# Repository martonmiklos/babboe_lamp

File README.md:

# Babboe lamp replacement board

Heavily overengineered replacement board for Babboe headlight.

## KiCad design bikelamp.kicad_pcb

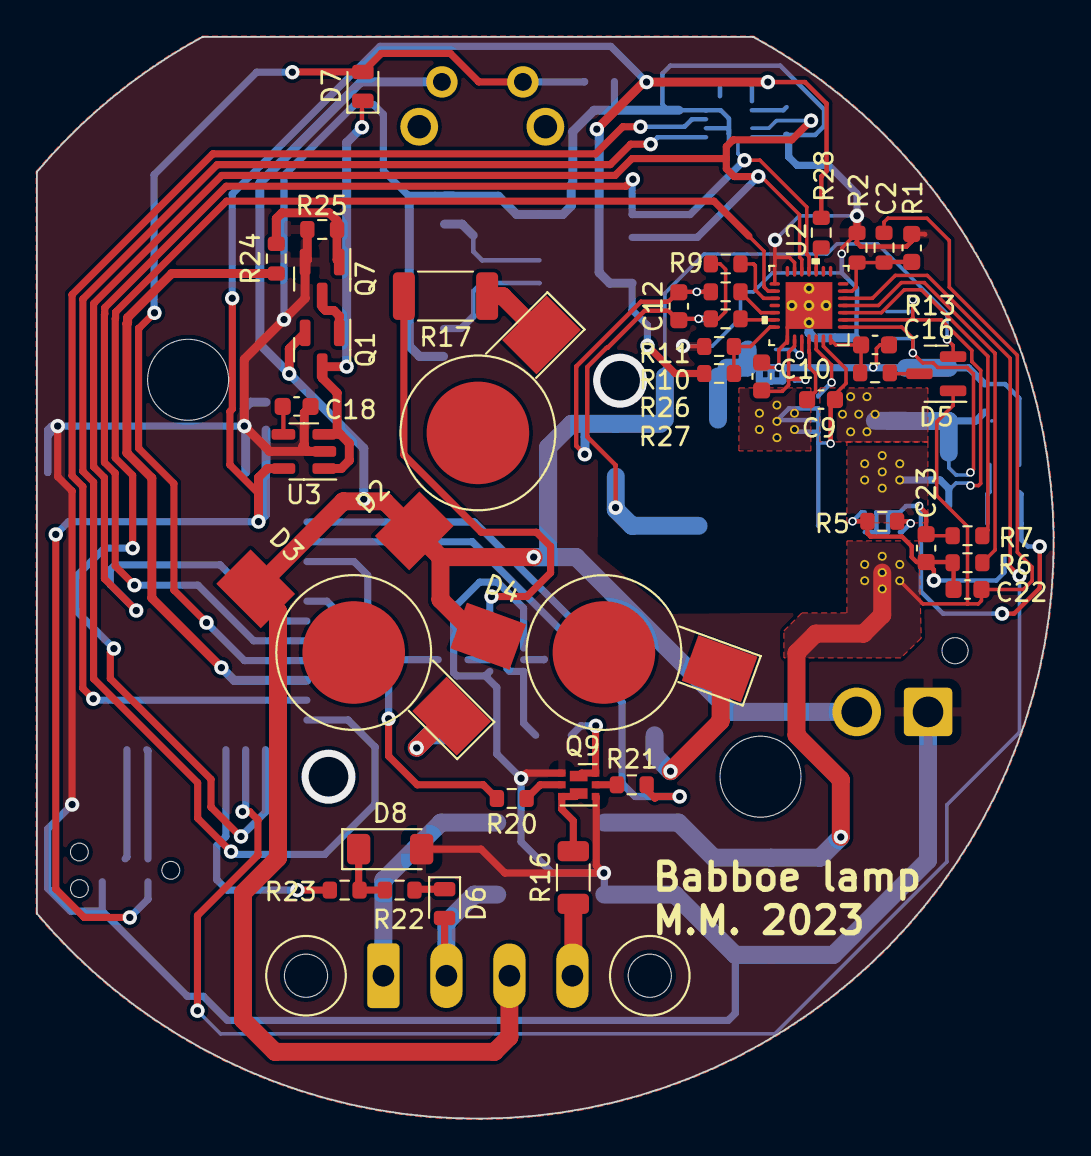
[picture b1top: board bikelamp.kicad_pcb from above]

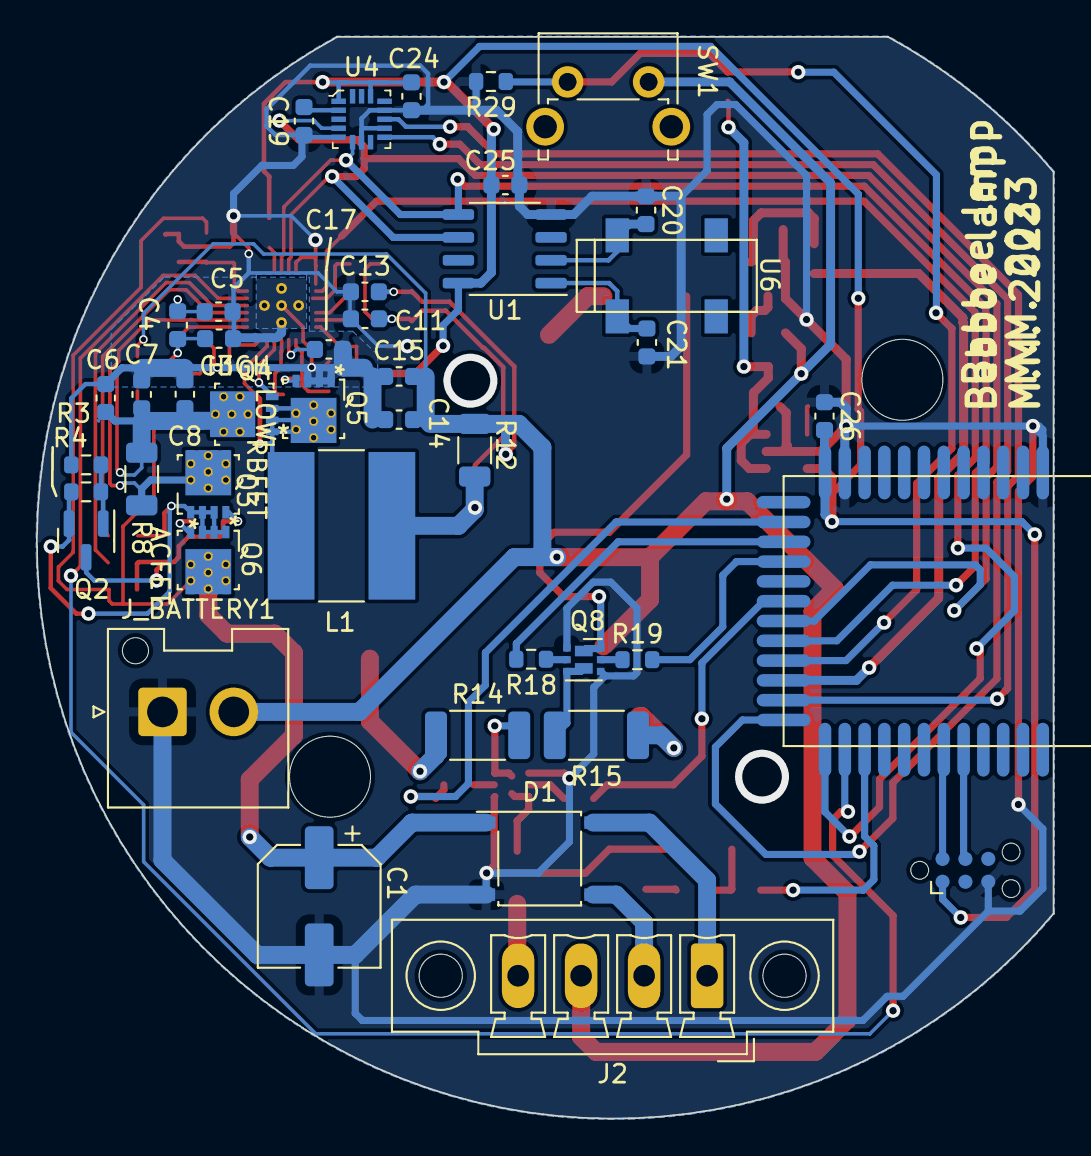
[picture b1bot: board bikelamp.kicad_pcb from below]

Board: 2 copper layers, 56.5 x 60.1 mm, 85 parts (45 on the bottom side), 66 nets.

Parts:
C1: 100uF; CP_Elec_6.3x5.7
C2, C3, C4, C5, C11, C12, C13, C19, C24, C25, C26: 100nF; C_0603_1608Metric
C6, C16: 1uF; C_0603_1608Metric
C7, C8, C14, C15: 10uF; C_0603_1608Metric
C9, C23: 47nF; C_0603_1608Metric
C10, C18: 470pF; C_0603_1608Metric
C17: 2u2; C_0603_1608Metric
C20, C21: 5pF; C_0603_1608Metric
C22: 1nF; C_0603_1608Metric
D1: D_Bridge_+-AA; Diode_Bridge_Diotec_ABS
D2, D3, D4: LED; LED_1W_3W_R8
D5: BAT54C; SOT-23
D6, D7: D_Schottky; D_MicroMELF
D8: BZV55C2V7; D_MiniMELF
J1: Conn_ARM_SWD_TagConnect_TC2030-NL; Tag-Connect_TC2030-IDC-NL_2x03_P1.27mm_Vertical
J2: Conn_01x04_Pin; PhoenixContact_MCV_1,5_4-GF-3.5_1x04_P3.50mm_Vertical_Threa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
J_BATTERY1: Conn_01x02; JST_VH_B2P-VH-FB-B_1x02_P3.96mm_Vertical
L1: 3,3uH; L_Bourns-SRN8040_8x8.15mm
NT1, NT2: NetTie_2; NetTie-2_SMD_Pad0.5mm
Q1: Q_PMOS_GSD; SOT-23
Q2, Q7: BSS138; SOT-23
Q3: RBFET; CSD18543Q3A
Q4: HIGH; CSD18543Q3A
Q5: LOW; CSD18543Q3A
Q6: ACFET; CSD18543Q3A
Q8, Q9: YJQ3400A-YAN; DFN2020-6L
R1: 430K; R_0603_1608Metric
R2: 66K5; R_0603_1608Metric
R3: 1M; R_0603_1608Metric
R4: 3M; R_0603_1608Metric
R5: 4R7; R_0603_1608Metric
R6, R7: 4K02; R_0603_1608Metric
R8, R12: 10m; R_1206_3216Metric
R9, R10, R11, R13: 10; R_0603_1608Metric
R14, R15, R17: TBD; R_2010_5025Metric
R16: TBD; R_1206_3216Metric
R18, R19, R20, R21: 100; R_0603_1608Metric
R22, R23: 1K; R_0603_1608Metric
R24: 47; R_0603_1608Metric
R25, R28, R29: 10K; R_0603_1608Metric
R26, R27: TBD; R_0603_1608Metric
SW1: SW_MEC_5E; SW_Tactile_SPST_Angled_PTS645Vx39-2LFS
U1: MCP79402T-xSN; SO-8_3.9x4.9mm_P1.27mm
U2: RUY0028A; BQ24780SRUYR
U3: MIC5205-3.3YM5; SOT-23-5
U4: MMA8452QR1; VQFN-16_3x3mm
U5: YJ-14015
U6: MC-306

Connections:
+3V3: C24.2, C25.2, C26.2, J1.1 (VCC), R27.1, R28.1, U1.8 (VCC), U3.5 (OUT), U4.1 (VDDIO), U4.14 (VDD), U5.12 (VCC)
/BQ24780/ACDRV: R6.2, U2.4 (ACDRV)
/BQ24780/ACFET_GATE: Q6.4 (G), R5.1
/BQ24780/BATSRC: R9.1, U2.17 (BATSRC)
/BQ24780/BTST: C9.1, U2.25 (BTST)
/BQ24780/CMSRC: R7.2, U2.3 (CMSRC)
/BQ24780/HIDRV: Q4.4 (G), U2.26 (HIDRV)
/BQ24780/ILIM: R26.1, R27.2, U2.21 (ILIM)
/BQ24780/LODRV: C10.2, Q5.4 (G), U2.23 (LODRV)
/BQ24780/PHASE: C9.2, L1.1, Q4.1 (S), Q4.2 (S), Q4.3 (S), Q5.5 (D), Q5.6 (D), Q5.7 (D), Q5.8 (D), Q5.9 (D), U2.27 (PHASE)
/BQ24780/RBFET_GATE: C22.1, C23.1, Q2.3 (D), Q3.4 (G), R5.2, R6.1
/BQ24780/SRN: R11.1, U2.19 (SRN)
/BQ24780/SRP: R10.1, U2.20 (SRP)
/BQ24780/SR_R_N: C12.2, C13.2, NT2.1, R11.2
/BQ24780/SR_R_P: C11.2, C12.1, L1.2, R9.2, R10.2, R12.1
/BQ24780/VCC_R: D5.3, R13.2
/BQ24780/VIN_I_MEASURED: C4.2, C5.2, C6.2, C7.2, C8.2, Q4.5 (D), Q4.6 (D), Q4.7 (D), Q4.8 (D), Q4.9 (D), R8.2, U2.1 (ACN)
/BQ24780/VIN_REVPROT: C3.2, C4.1, Q3.5 (D), Q3.6 (D), Q3.7 (D), Q3.8 (D), Q3.9 (D), R8.1, U2.2 (ACP)
/BQ24780/VIN_SWITCHABLE: C23.2, Q2.2 (S), Q3.1 (S), Q3.2 (S), Q3.3 (S), Q6.1 (S), Q6.2 (S), Q6.3 (S), R4.2, R7.1
/LEDs/LED1_GATE_R: Q8.2 (G), R18.1
/LEDs/LED2_GATE_R: Q8.5 (G), R19.1
/LEDs/LED3_GATE_R: Q9.2 (G), R20.1
ACOK: U2.5 (ACOK), U5.26 (P12)
GND: C1.2, C2.2, C3.1, C5.1, C11.1, C13.1, C18.1, C19.1, C20.1, C21.1, C24.1, C25.1, C26.1, D1.2 (-), D8.2 (A), J1.5 (GND), J_BATTERY1.1, NT1.1, Q7.2 (S), Q8.1 (S), Q8.4 (S), Q9.1 (S), Q9.4 (S), R2.2, R25.2, R26.2, R29.2, U1.4 (VSS), U2.13 (CMPIN), U2.15 (BATPRES_N), U3.2 (GND), U4.5 (GND), U4.7 (SA0), U4.10 (GND), U4.12 (GND), U5.1 (GND), U5.11 (GND)
GNDPWR: C6.1, C7.1, C8.1, C10.1, C14.1, C15.1, C16.1, C17.1, NT1.2, Q5.1 (S), Q5.2 (S), Q5.3 (S), R3.1, U2.22 (GND), U2.29 (PAD)
KEEP_POWER: R24.1, U5.22 (P08)
LED_PWM_0: R18.2, U5.15 (P01)
LED_PWM_1: R19.2, U5.16 (P02)
LED_PWM_2: R21.2, U5.14 (P00)
LED_PWM_3: R20.2, U5.18 (P04)
MMA8452_INT1: U4.11 (INT1), U5.23 (P09)
MMA8452_INT2: U4.9 (INT2), U5.24 (P10)
unnamed: D2.1 (K), R17.1
unnamed: D3.1 (K), R15.1
unnamed: D4.1 (K), R14.1
unnamed: D1.3, D6.2 (A), J2.2
unnamed: D6.1 (K), R22.2
unnamed: D7.1 (K), Q1.3 (D), U3.1 (IN), U3.3 (EN)
unnamed: D8.1 (K), R22.1, R23.2
unnamed: D1.4, J2.1
unnamed: Q1.1 (G), Q7.3 (D)
unnamed: Q2.1 (G), R3.2, R4.1
unnamed: Q7.1 (G), R24.2, R25.1
unnamed: Q8.6 (D), R17.2
unnamed: Q8.3 (D), R15.2
unnamed: Q9.6 (D), R14.2
unnamed: Q9.3 (D), R16.2
unnamed: Q9.5 (G), R21.1
unnamed: C21.2, U1.1 (X1), U6.1 (D1)
unnamed: C20.2, U1.2 (X2), U6.4 (D4)
unnamed: C2.1, R1.2, R2.1, U2.6 (ACDET)
unnamed: R28.2, U2.10 (PROCHOT_N)
unnamed: C17.2, U2.24 (REGN)
unnamed: C18.2, U3.4 (BP)
unnamed: C19.2, U4.2 (BYP)
PWR_BTN_PRESSED: D7.2 (A), R29.1, SW1.1, U5.21 (P07)
REAR_LAMP_K: J2.4, R16.1
SCL: U1.6 (SCL), U2.12 (SCL), U4.4 (SCL), U5.19 (P05)
SDA: U1.5 (SDA), U2.11 (SDA), U4.6 (SDA), U5.20 (P06)
SWCLK: J1.4 (SWCLK), U5.32 (SWCLK)
SWDIO: J1.2 (SWDIO), U5.31 (SWDIO)
TB_STAT: U2.16 (TB_STAT_N), U5.25 (P11)
VBAT: C14.2, C15.2, D2.2 (A), D3.2 (A), D4.2 (A), D5.2, J2.3, J_BATTERY1.2, NT2.2, Q1.2 (S), R12.2, SW1.2
VCC: C16.2, R13.1, U2.28 (VCC)
VDD: C1.1, C22.2, D1.1 (+), D5.1, Q6.5 (D), Q6.6 (D), Q6.7 (D), Q6.8 (D), Q6.9 (D), R1.1
WHEEL_SIGNAL: R23.1, U5.27 (P13)

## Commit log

2022-12-20 Initial add after BQ24780 section routed
2022-12-28 Replaced BLE module with YJ-xxx
2023-01-06 Working on contours
2023-01-07 Added gate protection circuit to the SCH
2023-02-17 ERC pass
2023-02-17 Board routed
2023-02-22 - Get rid from <0.3 mm drills - Fine tune GND fill
